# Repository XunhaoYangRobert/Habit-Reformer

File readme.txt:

Technical summary
The habit reformer aims to solve the nuisances of our unhealthy habit that potentially influences our life quality and fitness. 
We mainly employ wearable device that is light enough and convenient for users to use. Through these wearable device like crossed-leg eavesdropper, we help consumers get rid of some unhealthy habit. Our wearable devices mainly help consumers realize the unintentional move or posture and correct it. 
The crossed-leg eavesdropper(CLE), our very first prototype, is a sticker-like device which can detect users¡¯ current leg condition to see whether they are doing crossed-legs. The CLE¡¯s sticker is a changeable Velcro that can stick on users¡¯ pants. Then the CLE is able to detect the relative position and pressure of two legs and judge whether the consumer is crossing their legs. 
As the CLE detects that the user is crossing their legs, the CLE will vibrate to make the user aware and put down their legs. Users can change the mode in the Settings of APP if they consider vibration is not an effective alarming way, a little electricity discharge, for example. 
We also have an application on Android that can gather data from wearable device and analyze it. It can tell you whether your habit is already healthy, or need to make an effort. The app make decision through daily detection. The data transits from device to phone through Bluetooth. 
The application records the data from hardware device. In the APP users are able to find the summary data of a week or a month. And the APP will also provide analysis. For example, list out the time user most likely to cross the legs in a day, a week and a month. 
In the second stage of our development, the consumer group is large enough and our products are diverse. Then, our products pursues to create a community where people care their health from daily habits. People in the community share thoughts and healthy experience not limited by the products on our application. The users are required to register accounts where they can record the data beyond one phone to a reachable account. During the first login, the App will require a series of information from users and scan the users¡¯ body to find some physical posture problem like uneven shoulder. Later the APP will provide you some articles about how to solve your problem and recommend the products that fit the condition.

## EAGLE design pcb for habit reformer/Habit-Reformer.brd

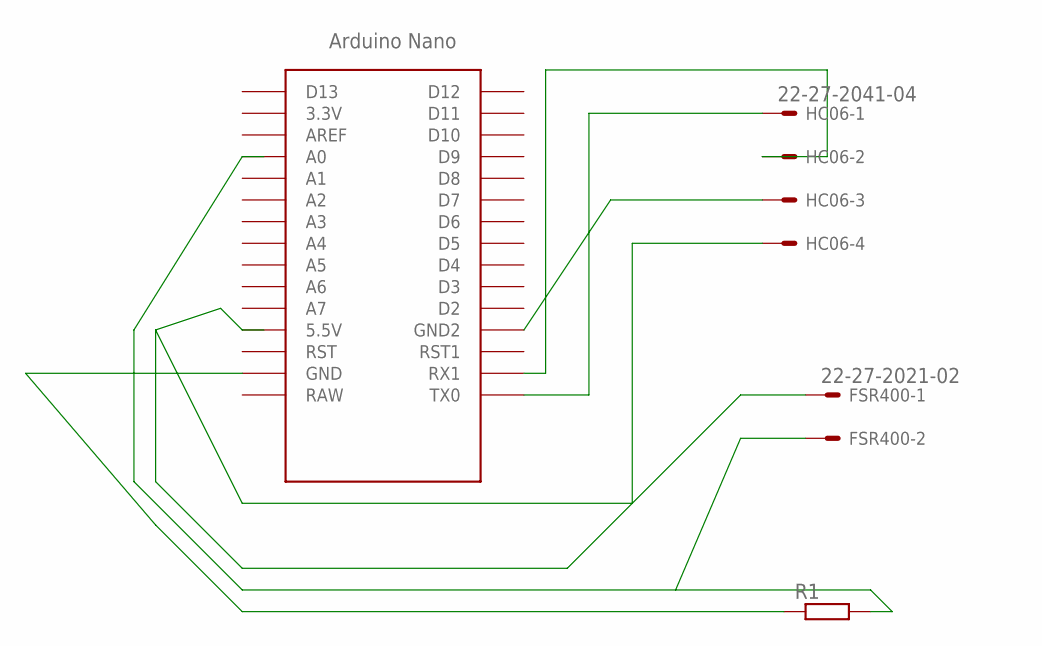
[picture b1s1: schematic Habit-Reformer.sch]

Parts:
FSR400: 22-27-2021-02; 6410-02
HC06: 22-27-2041-04; 6410-04
R1: R-EU_0204/7; 0204/7
U$1: NANO

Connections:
unnamed: HC06.1, U$1.TX0
unnamed: HC06.2, U$1.RX1
unnamed: HC06.3, U$1.GND1 (GND2)
unnamed: FSR400.1, HC06.4, U$1.5V (5.5V)
unnamed: FSR400.2, R1.2, U$1.A0
unnamed: R1.1, U$1.GND

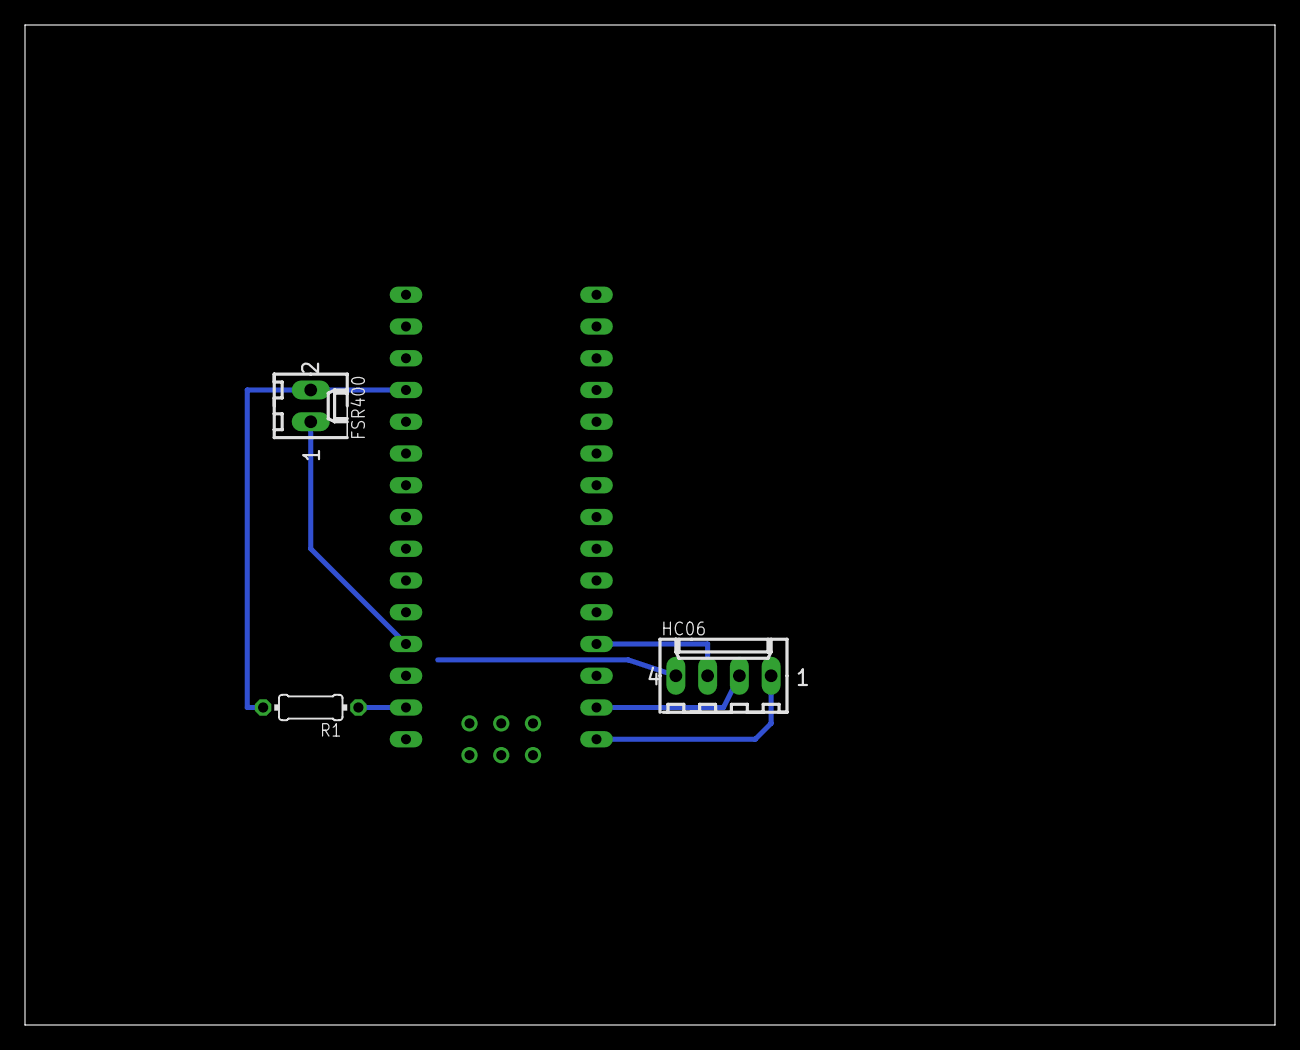
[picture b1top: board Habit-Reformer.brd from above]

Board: 2 copper layers, 100.0 x 80.0 mm, 4 parts (0 on the bottom side), 6 nets.

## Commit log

2018-01-20 Arduino-code
2018-01-20 PCB for Habit-Reformer
2018-01-20 Readme
2018-01-20 PCB update
